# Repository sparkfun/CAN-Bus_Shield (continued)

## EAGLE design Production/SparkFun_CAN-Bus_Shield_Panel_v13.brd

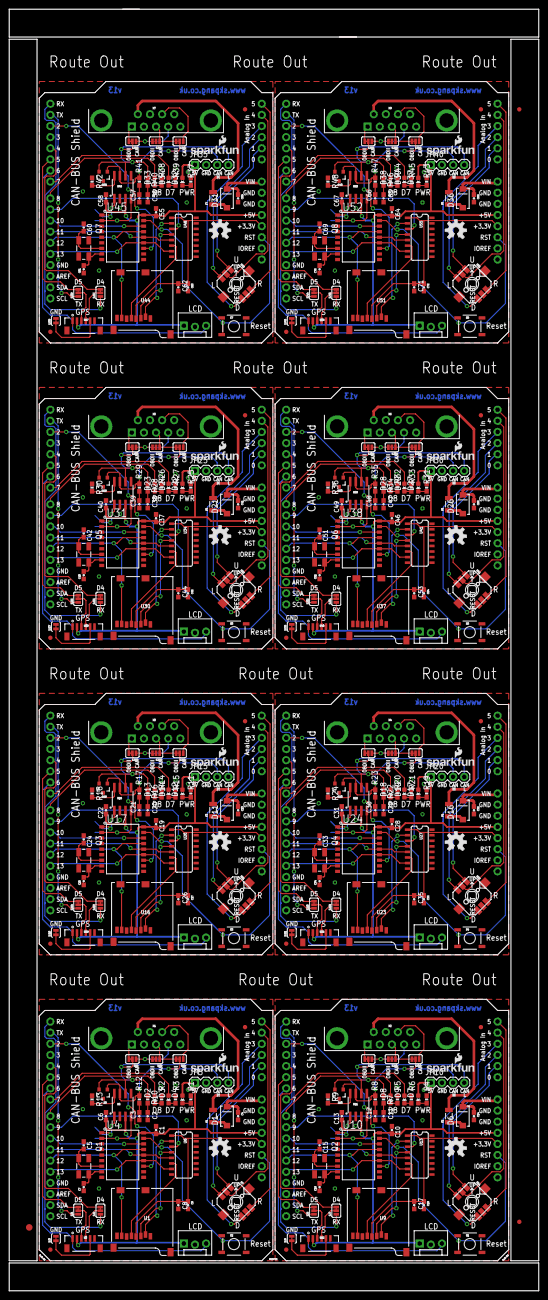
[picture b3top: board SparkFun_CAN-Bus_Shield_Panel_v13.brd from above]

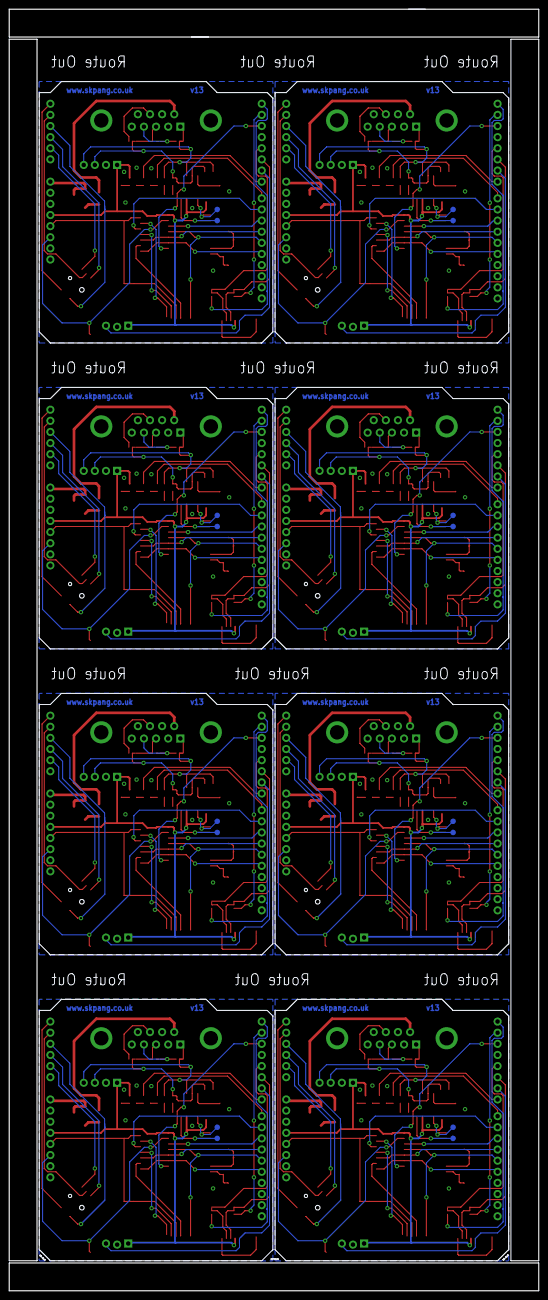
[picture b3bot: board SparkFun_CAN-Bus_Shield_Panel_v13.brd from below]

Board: 2 copper layers, 120.9 x 292.6 mm, 363 parts (16 on the bottom side), 376 nets.

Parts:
C1, C6, C8, C10, C13, C17, C19, C22, C26, C28, C31, C35, C37, C40, C44, C46, C49, C53, C55, C58, C62, C64, C67, C71: 0.1uF; 0603-CAP
C2, C3, C11, C12, C20, C21, C29, C30, C38, C39, C47, C48, C56, C57, C65, C66: 560pF; 0603-CAP
C4, C14, C23, C32, C41, C50, C59, C68: 4.7uF; 0603-CAP
C5, C7, C15, C16, C24, C25, C33, C34, C42, C43, C51, C52, C60, C61, C69, C70: 22pF; 0603-CAP
C9, C18, C27, C36, C45, C54, C63, C72: 1.0uF; 0603-CAP
D1, D6, D11, D16, D21, D26, D31, D36: MBRA140; SMA-DIODE
D2, D3, D8, D9, D13, D14, D18, D19, D23, D24, D28, D29, D33, D34, D38, D39: GREEN; LED-0603
D4, D7, D12, D17, D22, D27, D32, D37: RED; LED-0603
D5, D10, D15, D20, D25, D30, D35, D40: PESD1CAN; SOT23-3
E$1: FIDUCIAL-1.5X3
E$4, E$5: FIDUCIAL-1X2
F1, F2, F3, F4, F5, F6, F7, F8: PTC-1206
JP1, JP8, JP13, JP18, JP23, JP28, JP33, JP38: DNP; MOLEX-1X3_LOCK
JP2, JP3, JP6, JP7, JP11, JP12, JP16, JP17, JP21, JP22, JP26, JP27, JP31, JP32, JP36, JP37: FIDUCIAL1X2; FIDUCIAL-1X2
JP4, JP9, JP14, JP19, JP24, JP29, JP34, JP39: SFE_LOGO_NAME_FLAME.1_INCH; SFE_LOGO_NAME_FLAME_.1
JP5, JP10, JP15, JP20, JP25, JP30, JP35, JP40: DNP; 1X04
LOGO1, LOGO2, LOGO3, LOGO4, LOGO5, LOGO6, LOGO7, LOGO8: OSHW-LOGOM; OSHW-LOGO-M
Q1, Q2, Q3, Q4, Q5, Q6, Q7, Q8: 16MHz; CRYSTAL-SMD-5X3
R1, R2, R3, R4, R5, R6, R11, R14, R15, R19, R20, R21, R25, R26, R27, R31, R32, R33, R37, R38, R39, R43, R44, R45: 1K; 0603-RES
R7, R8, R10, R12, R16, R17, R22, R23, R28, R29, R34, R35, R40, R41, R46, R47: 100; 0603-RES
R9, R13, R18, R24, R30, R36, R42, R48: 4.7K; 0603-RES
S1, S2, S3, S4, S5, S6, S7, S8: RESET; TACTILE-SWITCH-SMD
SJ1, SJ2, SJ4, SJ5, SJ6, SJ7, SJ8, SJ10, SJ11, SJ12, SJ13, SJ14, SJ16, SJ17, SJ18, SJ19, SJ20, SJ22, SJ23, SJ24, SJ25, SJ26, SJ28, SJ29, SJ30, SJ31, SJ32, SJ34, SJ35, SJ36, SJ37, SJ38, SJ40, SJ41, SJ42, SJ43, SJ44, SJ46, SJ47, SJ48: JUMPER-PAD-3-2OF3_NC_BY_TRACE_SMALL; PAD-JUMPER-3-2OF3_NC_BY_TRACE_YES_SILK_FULL_BOX
SJ3, SJ9, SJ15, SJ21, SJ27, SJ33, SJ39, SJ45: JUMPER-PAD-2-NC_BY_TRACE; PAD-JUMPER-2-NC_BY_TRACE_YES_SILK
TP1, TP2, TP3, TP4, TP5, TP6, TP7, TP8, TP9, TP10, TP11, TP12, TP13, TP14, TP15, TP16: TEST-POINT3X5; PAD.03X.05
U1, U9, U16, U23, U30, U37, U44, U51: USD-SOCKET; MICROSD_1:1
U2, U8, U15, U22, U29, U36, U43, U50: ARDUINO_R3_SHIELD; UNO_R3_SHIELD
U3, U12, U19, U26, U33, U40, U47, U54: JST_VERTICAL; JST-6-SMD-VERT-1.0MM
U4, U10, U17, U24, U31, U38, U45, U52: MCP2515; SO-18W
U5, U11, U18, U25, U32, U39, U46, U53: MCP2551; SO08
U6, U13, U20, U27, U34, U41, U48, U55: HEX_CONVERTER; SO016
U7, U14, U21, U28, U35, U42, U49, U56: JOYSTICK_MINI
X1, X2, X3, X4, X5, X6, X7, X8: DB9 Plug; DB9_MALE

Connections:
3.3V: C8.2, C9.1, U1.4, U2.3.3V, U6.1
3.3V1: C17.2, C18.1, U8.3.3V, U9.4, U13.1
3.3V2: C26.2, C27.1, U15.3.3V, U16.4, U20.1
3.3V3: C35.2, C36.1, U22.3.3V, U23.4, U27.1
3.3V4: C44.2, C45.1, U29.3.3V, U30.4, U34.1
3.3V5: C53.2, C54.1, U36.3.3V, U37.4, U41.1
3.3V6: C62.2, C63.1, U43.3.3V, U44.4, U48.1
3.3V7: C71.2, C72.1, U50.3.3V, U51.4, U55.1
5V: C1.2, C6.2, D4.A, JP1.1, JP5.1, U2.5V, U3.2, U4.18, U5.3
5V1: C10.2, C13.2, D7.A, JP8.1, JP10.1, U8.5V, U10.18, U11.3, U12.2
5V2: C19.2, C22.2, D12.A, JP13.1, JP15.1, U15.5V, U17.18, U18.3, U19.2
5V3: C28.2, C31.2, D17.A, JP18.1, JP20.1, U22.5V, U24.18, U25.3, U26.2
5V4: C37.2, C40.2, D22.A, JP23.1, JP25.1, U29.5V, U31.18, U32.3, U33.2
5V5: C46.2, C49.2, D27.A, JP28.1, JP30.1, U36.5V, U38.18, U39.3, U40.2
5V6: C55.2, C58.2, D32.A, JP33.1, JP35.1, U43.5V, U45.18, U46.3, U47.2
5V7: C64.2, C67.2, D37.A, JP38.1, JP40.1, U50.5V, U52.18, U53.3, U54.2
12V: C4.1, D1.C, U2.VIN
12V1: C14.1, D6.C, U8.VIN
12V2: C23.1, D11.C, U15.VIN
12V3: C32.1, D16.C, U22.VIN
12V4: C41.1, D21.C, U29.VIN
12V5: C50.1, D26.C, U36.VIN
12V6: C59.1, D31.C, U43.VIN
12V7: C68.1, D36.C, U50.VIN
CANH: D5.1, JP5.3, R12.2, SJ4.2, U5.7
CANH1: D10.1, JP10.3, R8.2, SJ10.2, U11.7
CANH2: D15.1, JP15.3, R17.2, SJ16.2, U18.7
CANH3: D20.1, JP20.3, R23.2, SJ22.2, U25.7
CANH4: D25.1, JP25.3, R29.2, SJ28.2, U32.7
CANH5: D30.1, JP30.3, R35.2, SJ34.2, U39.7
CANH6: D35.1, JP35.3, R41.2, SJ40.2, U46.7
CANH7: D40.1, JP40.3, R47.2, SJ46.2, U53.7
CANL: D5.2, JP5.4, R10.2, SJ6.2, U5.6
CANL1: D10.2, JP10.4, R7.2, SJ12.2, U11.6
CANL2: D15.2, JP15.4, R16.2, SJ18.2, U18.6
CANL3: D20.2, JP20.4, R22.2, SJ24.2, U25.6
CANL4: D25.2, JP25.4, R28.2, SJ30.2, U32.6
CANL5: D30.2, JP30.4, R34.2, SJ36.2, U39.6
CANL6: D35.2, JP35.4, R40.2, SJ42.2, U46.6
CANL7: D40.2, JP40.4, R46.2, SJ48.2, U53.6
CAN_CS: U2.D10, U4.16
CAN_CS1: U8.D10, U10.16
CAN_CS2: U15.D10, U17.16
CAN_CS3: U22.D10, U24.16
CAN_CS4: U29.D10, U31.16
CAN_CS5: U36.D10, U38.16
CAN_CS6: U43.D10, U45.16
CAN_CS7: U50.D10, U52.16
CAN_INT: U2.D2, U4.12
CAN_INT1: U8.D2, U10.12
CAN_INT2: U15.D2, U17.12
CAN_INT3: U22.D2, U24.12
CAN_INT4: U29.D2, U31.12
CAN_INT5: U36.D2, U38.12
CAN_INT6: U43.D2, U45.12
CAN_INT7: U50.D2, U52.12
CAN_RXD: TP1.P$1, U4.2, U5.4
CAN_RXD1: TP3.P$1, U10.2, U11.4
CAN_RXD2: TP5.P$1, U17.2, U18.4
CAN_RXD3: TP7.P$1, U24.2, U25.4
CAN_RXD4: TP9.P$1, U31.2, U32.4
CAN_RXD5: TP11.P$1, U38.2, U39.4
CAN_RXD6: TP13.P$1, U45.2, U46.4
CAN_RXD7: TP15.P$1, U52.2, U53.4
CAN_TXD: TP2.P$1, U4.1, U5.1
CAN_TXD1: TP4.P$1, U10.1, U11.1
CAN_TXD2: TP6.P$1, U17.1, U18.1
CAN_TXD3: TP8.P$1, U24.1, U25.1
CAN_TXD4: TP10.P$1, U31.1, U32.1
CAN_TXD5: TP12.P$1, U38.1, U39.1
CAN_TXD6: TP14.P$1, U45.1, U46.1
CAN_TXD7: TP16.P$1, U52.1, U53.1
D1: SJ7.3, U8.D4
D2: SJ8.3, U8.D5
D4: SJ2.3, U2.D4
D5: SJ1.3, U2.D5
D7: SJ13.3, U15.D4
D8: SJ14.3, U15.D5
D10: SJ19.3, U22.D4
D11: SJ20.3, U22.D5
D13: SJ25.3, U29.D4
D14: SJ26.3, U29.D5
D16: SJ31.3, U36.D4
D17: SJ32.3, U36.D5
D19: SJ37.3, U43.D4
D20: SJ38.3, U43.D5
D22: SJ43.3, U50.D4
D23: SJ44.3, U50.D5
GND: C1.1, C2.1, C3.1, C4.2, C5.1, C6.1, C7.1, C8.1, C9.2, D5.3, JP1.2, JP5.2, R1.1, R2.1, R3.1, R13.1, S2.1, SJ3.2, SJ5.2, U1.6, U1.CD1, U1.CD2, U1.GND1, U1.GND3, U2.GND@0, U2.GND@1, U2.GND@2, U3.1, U4.9, U5.2, U6.8, U7.GND
GND1: C10.1, C11.1, C12.1, C13.1, C14.2, C15.1, C16.1, C17.1, C18.2, D10.3, JP8.2, JP10.2, R4.1, R5.1, R6.1, R9.1, S1.1, SJ9.2, SJ11.2, U8.GND@0, U8.GND@1, U8.GND@2, U9.6, U9.CD1, U9.CD2, U9.GND1, U9.GND3, U10.9, U11.2, U12.1, U13.8, U14.GND
GND2: C19.1, C20.1, C21.1, C22.1, C23.2, C24.1, C25.1, C26.1, C27.2, D15.3, JP13.2, JP15.2, R11.1, R14.1, R15.1, R18.1, S3.1, SJ15.2, SJ17.2, U15.GND@0, U15.GND@1, U15.GND@2, U16.6, U16.CD1, U16.CD2, U16.GND1, U16.GND3, U17.9, U18.2, U19.1, U20.8, U21.GND
GND3: C28.1, C29.1, C30.1, C31.1, C32.2, C33.1, C34.1, C35.1, C36.2, D20.3, JP18.2, JP20.2, R19.1, R20.1, R21.1, R24.1, S4.1, SJ21.2, SJ23.2, U22.GND@0, U22.GND@1, U22.GND@2, U23.6, U23.CD1, U23.CD2, U23.GND1, U23.GND3, U24.9, U25.2, U26.1, U27.8, U28.GND
GND4: C37.1, C38.1, C39.1, C40.1, C41.2, C42.1, C43.1, C44.1, C45.2, D25.3, JP23.2, JP25.2, R25.1, R26.1, R27.1, R30.1, S5.1, SJ27.2, SJ29.2, U29.GND@0, U29.GND@1, U29.GND@2, U30.6, U30.CD1, U30.CD2, U30.GND1, U30.GND3, U31.9, U32.2, U33.1, U34.8, U35.GND
GND5: C46.1, C47.1, C48.1, C49.1, C50.2, C51.1, C52.1, C53.1, C54.2, D30.3, JP28.2, JP30.2, R31.1, R32.1, R33.1, R36.1, S6.1, SJ33.2, SJ35.2, U36.GND@0, U36.GND@1, U36.GND@2, U37.6, U37.CD1, U37.CD2, U37.GND1, U37.GND3, U38.9, U39.2, U40.1, U41.8, U42.GND
GND6: C55.1, C56.1, C57.1, C58.1, C59.2, C60.1, C61.1, C62.1, C63.2, D35.3, JP33.2, JP35.2, R37.1, R38.1, R39.1, R42.1, S7.1, SJ39.2, SJ41.2, U43.GND@0, U43.GND@1, U43.GND@2, U44.6, U44.CD1, U44.CD2, U44.GND1, U44.GND3, U45.9, U46.2, U47.1, U48.8, U49.GND
GND7: C64.1, C65.1, C66.1, C67.1, C68.2, C69.1, C70.1, C71.1, C72.2, D40.3, JP38.2, JP40.2, R43.1, R44.1, R45.1, R48.1, S8.1, SJ45.2, SJ47.2, U50.GND@0, U50.GND@1, U50.GND@2, U51.6, U51.CD1, U51.CD2, U51.GND1, U51.GND3, U52.9, U53.2, U54.1, U55.8, U56.GND
JOY-CLICK: U2.A4, U7.CTR
JOY-CLICK1: U8.A4, U14.CTR
JOY-CLICK2: U15.A4, U21.CTR
JOY-CLICK3: U22.A4, U28.CTR
JOY-CLICK4: U29.A4, U35.CTR
JOY-CLICK5: U36.A4, U42.CTR
JOY-CLICK6: U43.A4, U49.CTR
JOY-CLICK7: U50.A4, U56.CTR
JOY-DOWN: U2.A3, U7.D
JOY-DOWN1: U8.A3, U14.D
JOY-DOWN2: U15.A3, U21.D
JOY-DOWN3: U22.A3, U28.D
JOY-DOWN4: U29.A3, U35.D
JOY-DOWN5: U36.A3, U42.D
JOY-DOWN6: U43.A3, U49.D
JOY-DOWN7: U50.A3, U56.D
JOY-LEFT: U2.A2, U7.C
JOY-LEFT1: U8.A2, U14.C
JOY-LEFT2: U15.A2, U21.C
JOY-LEFT3: U22.A2, U28.C
JOY-LEFT4: U29.A2, U35.C
JOY-LEFT5: U36.A2, U42.C
JOY-LEFT6: U43.A2, U49.C
JOY-LEFT7: U50.A2, U56.C
JOY-RIGHT: U2.A5, U7.B
JOY-RIGHT1: U8.A5, U14.B
JOY-RIGHT2: U15.A5, U21.B
JOY-RIGHT3: U22.A5, U28.B
JOY-RIGHT4: U29.A5, U35.B
JOY-RIGHT5: U36.A5, U42.B
JOY-RIGHT6: U43.A5, U49.B
JOY-RIGHT7: U50.A5, U56.B
JOY-UP: U2.A1, U7.A
JOY-UP1: U8.A1, U14.A
JOY-UP2: U15.A1, U21.A
JOY-UP3: U22.A1, U28.A
JOY-UP4: U29.A1, U35.A
JOY-UP5: U36.A1, U42.A
JOY-UP6: U43.A1, U49.A
JOY-UP7: U50.A1, U56.A
LCD: JP1.3, U2.D6
LCD1: JP8.3, U8.D6
LCD2: JP13.3, U15.D6
LCD3: JP18.3, U22.D6
LCD4: JP23.3, U29.D6
LCD5: JP28.3, U36.D6
LCD6: JP33.3, U43.D6
LCD7: JP38.3, U50.D6
LED1: D2.A, U2.D8
LED2: D3.A, U2.D7
LED3: D8.A, U8.D8
LED4: D9.A, U8.D7
LED5: D13.A, U15.D8
LED6: D14.A, U15.D7
LED7: D18.A, U22.D8
LED8: D19.A, U22.D7
LED9: D23.A, U29.D8
LED10: D24.A, U29.D7
LED11: D28.A, U36.D8
LED12: D29.A, U36.D7
LED13: D33.A, U43.D8
LED14: D34.A, U43.D7
LED15: D38.A, U50.D8
LED16: D39.A, U50.D7
MISO: U1.7, U2.D12, U4.15
MISO1: U8.D12, U9.7, U10.15
MISO2: U15.D12, U16.7, U17.15
MISO3: U22.D12, U23.7, U24.15
MISO4: U29.D12, U30.7, U31.15
MISO5: U36.D12, U37.7, U38.15
MISO6: U43.D12, U44.7, U45.15
MISO7: U50.D12, U51.7, U52.15
MOSI: U2.D11, U4.14, U6.5
MOSI1: U8.D11, U10.14, U13.5
MOSI2: U15.D11, U17.14, U20.5
MOSI3: U22.D11, U24.14, U27.5
MOSI4: U29.D11, U31.14, U34.5
MOSI5: U36.D11, U38.14, U41.5
MOSI6: U43.D11, U45.14, U48.5
MOSI7: U50.D11, U52.14, U55.5
unnamed: SJ3.1, U3.5
unnamed: SJ6.3, X1.5
unnamed: D8.C, R5.2
unnamed: D4.C, R1.2
unnamed: D2.C, R2.2
unnamed: D3.C, R3.2
unnamed: D9.C, R6.2
unnamed: C11.2, R7.1
unnamed: C2.2, R10.1
unnamed: C3.2, R12.1
unnamed: C12.2, R8.1
unnamed: R9.2, U11.8
unnamed: F1.2, X1.9
unnamed: R13.2, U5.8
unnamed: U1.2, U6.2
unnamed: D1.A, F1.1
unnamed: C7.2, Q1.3, U4.8
unnamed: C5.2, Q1.1, U4.7
unnamed: U1.3, U6.4
unnamed: F2.2, X2.9
unnamed: SJ1.2, U3.3
unnamed: SJ2.2, U3.4
unnamed: D6.A, F2.1
unnamed: U1.5, U6.6
unnamed: C16.2, Q2.3, U10.8
unnamed: C15.2, Q2.1, U10.7
unnamed: SJ8.2, U12.3
unnamed: SJ7.2, U12.4
unnamed: D7.C, R4.2
unnamed: U9.2, U13.2
unnamed: U9.3, U13.4
unnamed: U9.5, U13.6
unnamed: SJ9.1, U12.5
unnamed: SJ12.3, X2.5
unnamed: D13.C, R14.2
unnamed: D14.C, R15.2
unnamed: C20.2, R16.1
unnamed: C21.2, R17.1
unnamed: R18.2, U18.8
unnamed: F3.2, X3.9
unnamed: D11.A, F3.1
unnamed: C25.2, Q3.3, U17.8
unnamed: C24.2, Q3.1, U17.7
unnamed: SJ14.2, U19.3
unnamed: SJ13.2, U19.4
unnamed: D12.C, R11.2
unnamed: U16.2, U20.2
unnamed: U16.3, U20.4
unnamed: U16.5, U20.6
unnamed: SJ15.1, U19.5
unnamed: SJ18.3, X3.5
unnamed: D18.C, R20.2
unnamed: D19.C, R21.2
unnamed: C29.2, R22.1
unnamed: C30.2, R23.1
unnamed: R24.2, U25.8
unnamed: F4.2, X4.9
unnamed: D16.A, F4.1
unnamed: C34.2, Q4.3, U24.8
unnamed: C33.2, Q4.1, U24.7
unnamed: SJ20.2, U26.3
unnamed: SJ19.2, U26.4
unnamed: D17.C, R19.2
unnamed: U23.2, U27.2
unnamed: U23.3, U27.4
unnamed: U23.5, U27.6
unnamed: SJ21.1, U26.5
unnamed: SJ24.3, X4.5
unnamed: D23.C, R26.2
unnamed: D24.C, R27.2
unnamed: C38.2, R28.1
unnamed: C39.2, R29.1
unnamed: R30.2, U32.8
unnamed: F5.2, X5.9
unnamed: D21.A, F5.1
unnamed: C43.2, Q5.3, U31.8
unnamed: C42.2, Q5.1, U31.7
unnamed: SJ26.2, U33.3
unnamed: SJ25.2, U33.4
unnamed: D22.C, R25.2
unnamed: U30.2, U34.2
unnamed: U30.3, U34.4
unnamed: U30.5, U34.6
unnamed: SJ27.1, U33.5
unnamed: SJ30.3, X5.5
unnamed: D28.C, R32.2
unnamed: D29.C, R33.2
unnamed: C47.2, R34.1
unnamed: C48.2, R35.1
unnamed: R36.2, U39.8
unnamed: F6.2, X6.9
unnamed: D26.A, F6.1
unnamed: C52.2, Q6.3, U38.8
unnamed: C51.2, Q6.1, U38.7
unnamed: SJ32.2, U40.3
unnamed: SJ31.2, U40.4
unnamed: D27.C, R31.2
unnamed: U37.2, U41.2
unnamed: U37.3, U41.4
unnamed: U37.5, U41.6
unnamed: SJ33.1, U40.5
unnamed: SJ36.3, X6.5
unnamed: D33.C, R38.2
unnamed: D34.C, R39.2
unnamed: C56.2, R40.1
unnamed: C57.2, R41.1
unnamed: R42.2, U46.8
unnamed: F7.2, X7.9
unnamed: D31.A, F7.1
unnamed: C61.2, Q7.3, U45.8
unnamed: C60.2, Q7.1, U45.7
unnamed: SJ38.2, U47.3
unnamed: SJ37.2, U47.4
unnamed: D32.C, R37.2
unnamed: U44.2, U48.2
unnamed: U44.3, U48.4
unnamed: U44.5, U48.6
unnamed: SJ39.1, U47.5
unnamed: SJ42.3, X7.5
unnamed: D38.C, R44.2
unnamed: D39.C, R45.2
unnamed: C65.2, R46.1
unnamed: C66.2, R47.1
unnamed: R48.2, U53.8
unnamed: F8.2, X8.9
unnamed: D36.A, F8.1
unnamed: C70.2, Q8.3, U52.8
unnamed: C69.2, Q8.1, U52.7
unnamed: SJ44.2, U54.3
unnamed: SJ43.2, U54.4
unnamed: D37.C, R43.2
unnamed: U51.2, U55.2
unnamed: U51.3, U55.4
unnamed: U51.5, U55.6
unnamed: SJ45.1, U54.5
unnamed: SJ48.3, X8.5
PIN1: SJ10.3, SJ11.1, X2.3
PIN2: SJ5.3, SJ6.1, X1.2
PIN3: SJ4.3, SJ5.1, X1.3
PIN4: SJ10.1, X2.7
PIN5: SJ11.3, SJ12.1, X2.2
PIN6: SJ16.3, SJ17.1, X3.3
PIN7: SJ4.1, X1.7
PIN8: SJ16.1, X3.7
PIN9: SJ17.3, SJ18.1, X3.2
PIN10: SJ22.3, SJ23.1, X4.3
PIN11: SJ22.1, X4.7
PIN12: SJ23.3, SJ24.1, X4.2
PIN13: SJ28.3, SJ29.1, X5.3
PIN14: SJ28.1, X5.7
PIN15: SJ29.3, SJ30.1, X5.2
PIN16: SJ34.3, SJ35.1, X6.3
PIN17: SJ34.1, X6.7
PIN18: SJ35.3, SJ36.1, X6.2
PIN19: SJ40.3, SJ41.1, X7.3
PIN20: SJ40.1, X7.7
PIN21: SJ41.3, SJ42.1, X7.2
PIN22: SJ46.3, SJ47.1, X8.3
PIN23: SJ46.1, X8.7
PIN24: SJ47.3, SJ48.1, X8.2
RS: S2.3, U2.RES, U4.17
RS1: S1.3, U8.RES, U10.17
RS2: S3.3, U15.RES, U17.17
RS3: S4.3, U22.RES, U24.17
RS4: S5.3, U29.RES, U31.17
RS5: S6.3, U36.RES, U38.17
RS6: S7.3, U43.RES, U45.17
RS7: S8.3, U50.RES, U52.17
RX: SJ2.1, U2.RX
RX1: SJ7.1, U8.RX
RX2: SJ13.1, U15.RX
RX3: SJ19.1, U22.RX
RX4: SJ25.1, U29.RX
RX5: SJ31.1, U36.RX
RX6: SJ37.1, U43.RX
RX7: SJ43.1, U50.RX
SCK: U2.D13, U4.13, U6.7
SCK1: U8.D13, U10.13, U13.7
SCK2: U15.D13, U17.13, U20.7
SCK3: U22.D13, U24.13, U27.7
SCK4: U29.D13, U31.13, U34.7
SCK5: U36.D13, U38.13, U41.7
SCK6: U43.D13, U45.13, U48.7
SCK7: U50.D13, U52.13, U55.7
SD_CS: U2.D9, U6.3
SD_CS1: U8.D9, U13.3
SD_CS2: U15.D9, U20.3
SD_CS3: U22.D9, U27.3
SD_CS4: U29.D9, U34.3
SD_CS5: U36.D9, U41.3
SD_CS6: U43.D9, U48.3
SD_CS7: U50.D9, U55.3
TX: SJ1.1, U2.TX
TX1: SJ8.1, U8.TX
TX2: SJ14.1, U15.TX
TX3: SJ20.1, U22.TX
TX4: SJ26.1, U29.TX
TX5: SJ32.1, U36.TX
TX6: SJ38.1, U43.TX
TX7: SJ44.1, U50.TX

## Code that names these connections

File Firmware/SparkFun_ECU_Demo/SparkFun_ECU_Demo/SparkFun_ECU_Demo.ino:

/****************************************************************************
ECU CAN-Bus Reader and Logger

Toni Klopfenstein @ SparkFun Electronics
February 2015
https://github.com/sparkfun/CAN-Bus_Shield

This example sketch works with the CAN-Bus shield from SparkFun Electronics.

It enables reading of the MCP2515 CAN controller and MCP2551 CAN-Bus driver.
This sketch also enables logging of GPS data, and output to a serial-enabled LCD screen.
All data is logged to the uSD card. 

Resources:
Additional libraries to install for functionality of sketch.
-SD library by William Greiman. https://github.com/greiman/SdFat 
 
Development environment specifics:
Developed for Arduino 1.05

Based off of original example ecu_reader_logger by:
Sukkin Pang
SK Pang Electronics www.skpang.co.uk

This code is beerware; if you see me (or any other SparkFun employee) at the local, and you've found our code helpful, please buy us a round!
Distributed as-is; no warranty is given.
*************************************************************************/

//Include necessary libraries for compilation
#include <SD.h>
#include <SoftwareSerial.h>
#include <Canbus.h>
#include <TinyGPS.h>

//Initialize uSD pins
const int chipSelect = 9;

//Initialize lcd pins
SoftwareSerial lcd(3, 6);

//Initialize GPS pins
SoftwareSerial uart_gps(4,5);

// Define Joystick connection pins 
#define UP     A1
#define DOWN   A3
#define LEFT   A2
#define RIGHT  A5
#define CLICK  A4

//Define LED pins
#define LED2 8
#define LED3 7

//Define baud rates. GPS should be slower than serial to ensure valid sentences coming through
#define rate 115200;
#define GPS_Rate 4800;
#define LCD_Rate 115200;

//Create instance of TinyGPS
TinyGPS gps;

//Declare porototype for TinyGPS library functions
void getgps(TinyGPS &gps);

char buffer[512];

//Define LCD Positions
#define COMMAND 0xFE
#define CLEAR   0x01
#define LINE1  0x80
#define LINE2  0xC0


//********************************Setup Loop*********************************//
void setup() {
  //Initialize Serial communication for debugging
  Serial.begin(rate);
  Serial.println("ECU Demo");
  
  //Begin LCD serial communication
  lcd.begin(LCD_Rate);
  
  //Begin GPS communcation
  uart_gps.begin(GPS_Rate);
  
  //Initialize pins as necessary
  pinMode(chipSelect, OUTPUT);
  pinMode(UP,INPUT);
  pinMode(DOWN,INPUT);
  pinMode(LEFT,INPUT);
  pinMode(RIGHT,INPUT);
  pinMode(CLICK,INPUT);
  pinMode(LED2, OUTPUT);
  pinMode(LED3, OUTPUT);
  
  //Pull analog pins high to enable reading of joystick movements
  digitalWrite(UP, HIGH);
  digitalWrite(DOWN, HIGH);
  digitalWrite(LEFT, HIGH);
  digitalWrite(RIGHT, HIGH);
  digitalWrite(CLICK, HIGH);
  
  //Write LED pins low to turn them off by default
  digitalWrite(LED2, LOW);
  digitalWrite(LED3, LOW);
  
  //Check if uSD card initialized
  if (!SD.begin(chipSelect)) {
    Serial.println("uSD card failed to initialize, or is not present");
    return;
  }
  else{
      Serial.println("uSD card initialized.");
  } 
  
  //Print menu to LCD screen
  clear_lcd();
  lcd.print("Click to begin");
  lcd.write(COMMAND);
  lcd.write(LINE2);
  lcd.print("Logging Data");
  

}

//********************************Main Loop*********************************//
void loop(){
  
  File dataFile = SD.open("ECU_datalog.txt", FILE_WRITE);
  
  //If data file exists, write data to it
  if (dataFile){
    
    clear_lcd();
    lcd.print("Logging data");
    clear_lcd();
    lcd.print("Click joystick");
    lcd.write(COMMAND);
    lcd.write(LINE2);
    lcd.print("to stop logging");
    
    if(uart_gps.available())     // While there is data on the RX pin...
       {
         int c = uart_gps.read();    // load the data into a variable...
         if(gps.encode(c))      // if there is a new valid sentence...
         {
           getgps(gps);         // then grab the data.
         }
       }
     
    get_CAN(); //grab CAN data
     
    
    dataFile.println();
    dataFile.close();   //Close data logging file
  }
  //If file cannot be opened,write error to LCD screen
  else{
    clear_lcd();
    lcd.print("Error opening");
    lcd.write(COMMAND);
    lcd.write(LINE2);
    lcd.print("ECU_datalog.txt");
  }
  
}
//********************************CAN Bus Functions*********************************//

void get_CAN(void)
{
  Canbus.ecu_req(ENGINE_RPM,buffer); //Request engine RPM
  dataFile.print("Engine RPM: "); 
  dataFile.println(buffer);
  
  Canbus.ecu_req(VEHICLE_SPEED,buffer); //Request Vehicle speed
  dataFile.print("Vehicle speed: "); 
  dataFile.println(buffer);
  
  Canbus.ecu_req(ENGINE_COOLANT_TEMP,buffer); //Request engine coolant temp
  dataFile.print("Coolant temp: "); 
  dataFile.println(buffer);
  
  Canbus.ecu_req(THROTTLE, buffer); //Request throttle
  dataFile.print("Throttle: "); 
  dataFile.println(buffer);
 
  
}
//********************************LCD Functions*********************************//
void clear_lcd(void)
{
  lcd.write(COMMAND);
  lcd.write(CLEAR);
} 

//********************************GPS Functions*********************************//
void getgps(TinyGPS &gps)
{
  
  // Define the variables that will be used
  float latitude, longitude;
  // Then call this function
  gps.f_get_position(&latitude, &longitude);
  // You can now print variables latitude and longitude
  dataFile.print("Lat/Long: "); 
  dataFile.print(latitude,5); 
  dataFile.print(", "); 
  dataFile.println(longitude,5);
  
  // Same goes for date and time
  int year;
  byte month, day, hour, minute, second, hundredths;
  gps.crack_datetime(&year,&month,&day,&hour,&minute,&second,&hundredths);
  // Print data and time
  dataFile.print("Date: "); dataFile.print(month, DEC); dataFile.print("/"); 
  dataFile.print(day, DEC); dataFile.print("/"); dataFile.print(year);
  dataFile.print("  Time: "); dataFile.print(hour, DEC); dataFile.print(":"); 
  dataFile.print(minute, DEC); dataFile.print(":"); dataFile.print(second, DEC); 
  dataFile.print("."); dataFile.println(hundredths, DEC);
  //Since month, day, hour, minute, second, and hundr
  
  // Here you can print the altitude and course values directly since 
  // there is only one value for the function
  dataFile.print("Altitude(m): "); dataFile.println(gps.f_altitude());  
  // Same goes for course
  dataFile.print("Course(deg): "); dataFile.println(gps.f_course()); 
  // And same goes for speed
  dataFile.print("GPS Speed(kmph): "); dataFile.println(gps.f_speed_kmph());
  dataFile.println();
}

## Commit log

2013-11-19 Initial commit of board files and README
2013-11-25 Updating Board files to R3/Leonardo layout
2014-05-22 Fixing traces
2014-11-26 Midway changes for rev
2014-12-23 Schematic updates for QC checklist
2014-12-31 Adding in OBDII/CAN jumpers
2015-01-03 Adding ESD protection to CAN lines
2015-01-05 Adding in feedback from Sukkin, and engineering review/QC checklist
2015-01-05 Fixing DRC errors
2015-01-08 Pushing QC checklist changes
2015-01-08 Fixing test points
2015-02-06 Initial firmware commit
2015-02-09 Pusing additional demos
2015-04-09 Added production directory, updating shield units to pass QC check
2015-06-16 Updating to new uSD footprint, minor QC cleanup on schematic
2015-06-19 Fixing QC checks
2015-06-29 Updating PESD1CAN part to new library path
2015-07-01 created panel v13
2015-09-08 Adding Demo sketch-WIP
2015-09-08 Copying library files, updating sketch to remove serial error
2015-09-09 WIP demo sketches
2015-09-24 Moving example sketches into library example folder
2015-09-29 Updating sketches
2015-10-05 Cleaning up examples, removing duplicate files
2015-10-14 Updating repo structure
2015-10-14 Squashed 'Libraries/Arduino/' content from commit 1487658
    git-subtree-dir: Libraries/Arduino
    git-subtree-split: 1487658099556a8c6ec7d1cb3a7c75e15ad34a6e
2015-10-14 Updating README with new product info
2016-03-04 Fix PID conversion code
2016-03-15 Squashed 'Libraries/Arduino/' changes from 1487658..ffcd67b
    ffcd67b Fixing image URL
    939f654 @PlatformIO Library Registry manifest file
    git-subtree-dir: Libraries/Arduino
    git-subtree-split: ffcd67b7f4d5112f747f7c74a8677ef82a4ee202
2017-01-18 Squashed 'Libraries/Arduino/' changes from ffcd67b..99644e8
    99644e8 Adding additional demo sketches and updating library version
    git-subtree-dir: Libraries/Arduino
    git-subtree-split: 99644e84e184ecb8240c22ee06ea4a4871b766ba
2017-05-16 Fixed Link
2022-06-07 Start v20 update
    Ready for proto
